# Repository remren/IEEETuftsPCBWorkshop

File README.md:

# IEEETuftsPCBWorkshop
An introductory PCB workshop for the Tufts IEEE club using KiCad 7.0. The basis for this workshop is making a keyboard PCB, following these guides: [Masterzen's Guide](https://www.masterzen.fr/2020/05/03/designing-a-keyboard-part-1/) and [ai03's Guide](https://wiki.ai03.com/books/pcb-design/page/pcb-guide-part-1---preparations)

By learning how to make this PCB, hopefully one will be able use knowledge for other personal or work projects!

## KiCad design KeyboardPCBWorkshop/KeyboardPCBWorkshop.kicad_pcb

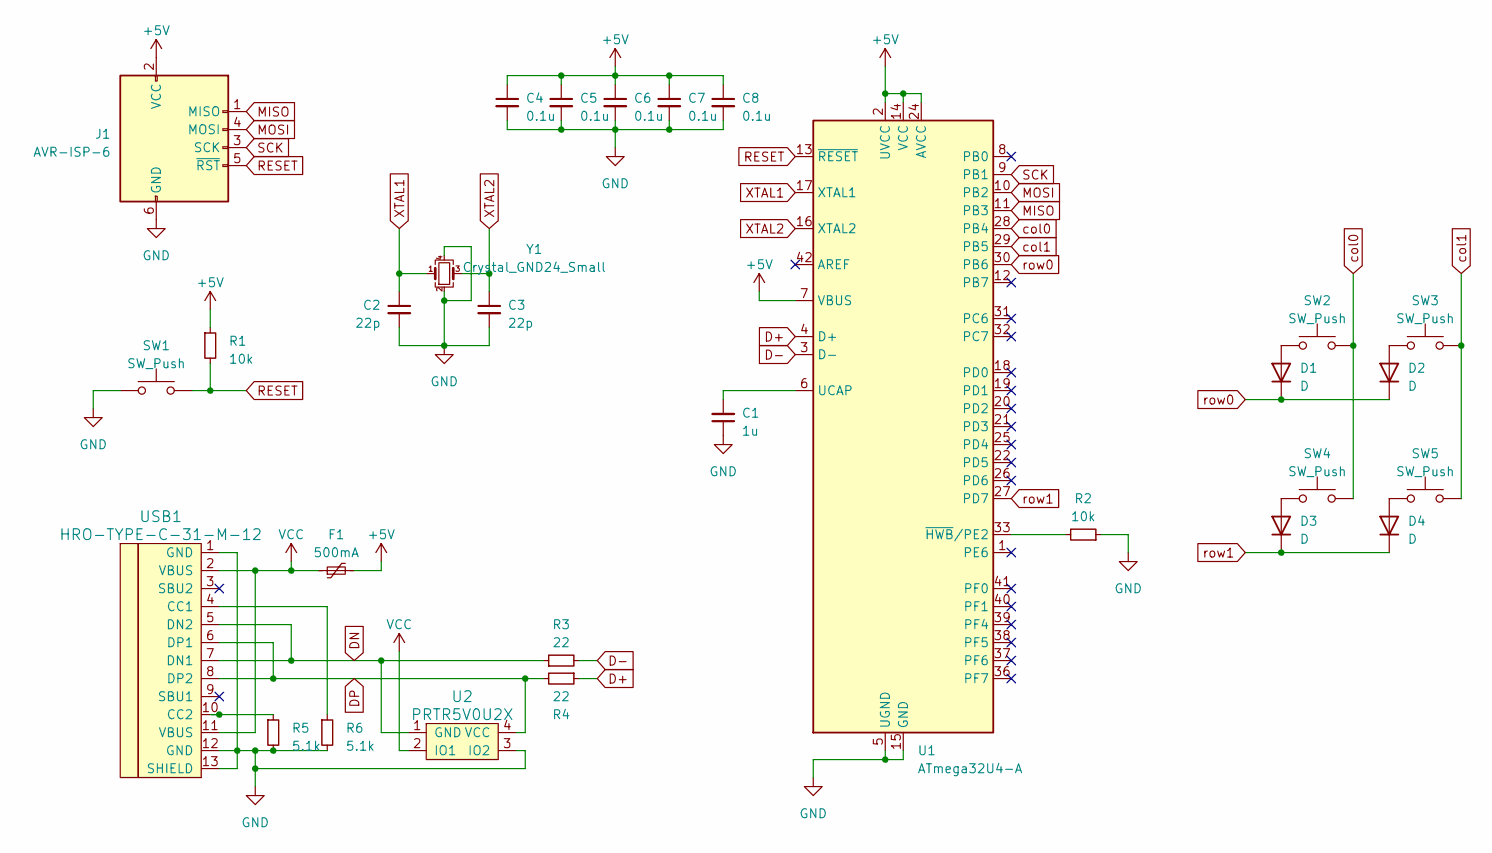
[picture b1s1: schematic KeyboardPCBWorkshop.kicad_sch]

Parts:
C1: 1u; C_0805_2012Metric_Pad1.18x1.45mm_HandSolder
C2, C3: 22p; C_0805_2012Metric_Pad1.18x1.45mm_HandSolder
C4, C5, C6, C7, C8: 0.1u; C_0805_2012Metric_Pad1.18x1.45mm_HandSolder
D1, D2, D3, D4: D; D_SOD-123
F1: 500mA; Fuse_1206_3216Metric_Pad1.42x1.75mm_HandSolder
J1: AVR-ISP-6; Reset_Pretty-Mask
R1, R2: 10k; R_0805_2012Metric_Pad1.20x1.40mm_HandSolder
R3, R4: 22; R_0805_2012Metric_Pad1.20x1.40mm_HandSolder
R5, R6: 5.1k; R_0805_2012Metric_Pad1.20x1.40mm_HandSolder
SW1: SW_Push; SW_SPST_SKQG_WithStem
SW2, SW3, SW4, SW5: SW_Push; MX-1U-NoLED
U1: ATmega32U4-A; TQFP-44_10x10mm_P0.8mm
U2: PRTR5V0U2X; SOT143B
USB1: HRO-TYPE-C-31-M-12; HRO-TYPE-C-31-M-12-HandSoldering
Y1: Crystal_GND24_Small; Crystal_SMD_3225-4Pin_3.2x2.5mm_HandSoldering

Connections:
+5V: C4.1, C5.1, C6.1, C7.1, C8.1, F1.2, J1.2 (VCC), R1.1, U1.2 (UVCC), U1.7 (VBUS), U1.14 (VCC), U1.24 (AVCC), U1.34 (VCC), U1.44 (AVCC)
D+: R4.1, U1.4 (D+)
D-: R3.2, U1.3 (D-)
DN: R3.1, U2.1 (GND), USB1.5 (DN2), USB1.7 (DN1)
DP: R4.2, U2.4 (VCC), USB1.6 (DP1), USB1.8 (DP2)
GND: C1.1, C2.2, C3.2, C4.2, C5.2, C6.2, C7.2, C8.2, J1.6 (GND), R2.1, R5.2, R6.2, SW1.1, U1.5 (UGND), U1.15 (GND), U1.23 (GND), U1.35 (GND), U1.43 (GND), U2.3 (IO2), USB1.1 (GND), USB1.12 (GND), USB1.13 (SHIELD), Y1.2, Y1.4
MISO: J1.1 (MISO), U1.11 (PB3)
MOSI: J1.4 (MOSI), U1.10 (PB2)
unnamed: D1.2 (A), SW2.2
unnamed: D2.2 (A), SW3.2
unnamed: D3.2 (A), SW4.2
unnamed: D4.2 (A), SW5.2
unnamed: C1.2, U1.6 (UCAP)
unnamed: R2.2, U1.33 (~HWB/PE2)
unnamed: R6.1, USB1.4 (CC1)
unnamed: R5.1, USB1.10 (CC2)
RESET: J1.5 (~RST), R1.2, SW1.2, U1.13 (~RESET)
SCK: J1.3 (SCK), U1.9 (PB1)
VCC: F1.1, U2.2 (IO1), USB1.2 (VBUS), USB1.11 (VBUS)
XTAL1: C2.1, U1.17 (XTAL1), Y1.1
XTAL2: C3.1, U1.16 (XTAL2), Y1.3
col0: SW2.1, SW4.1, U1.28 (PB4)
col1: SW3.1, SW5.1, U1.29 (PB5)
row0: D1.1 (K), D2.1 (K), U1.30 (PB6)
row1: D3.1 (K), D4.1 (K), U1.27 (PD7)

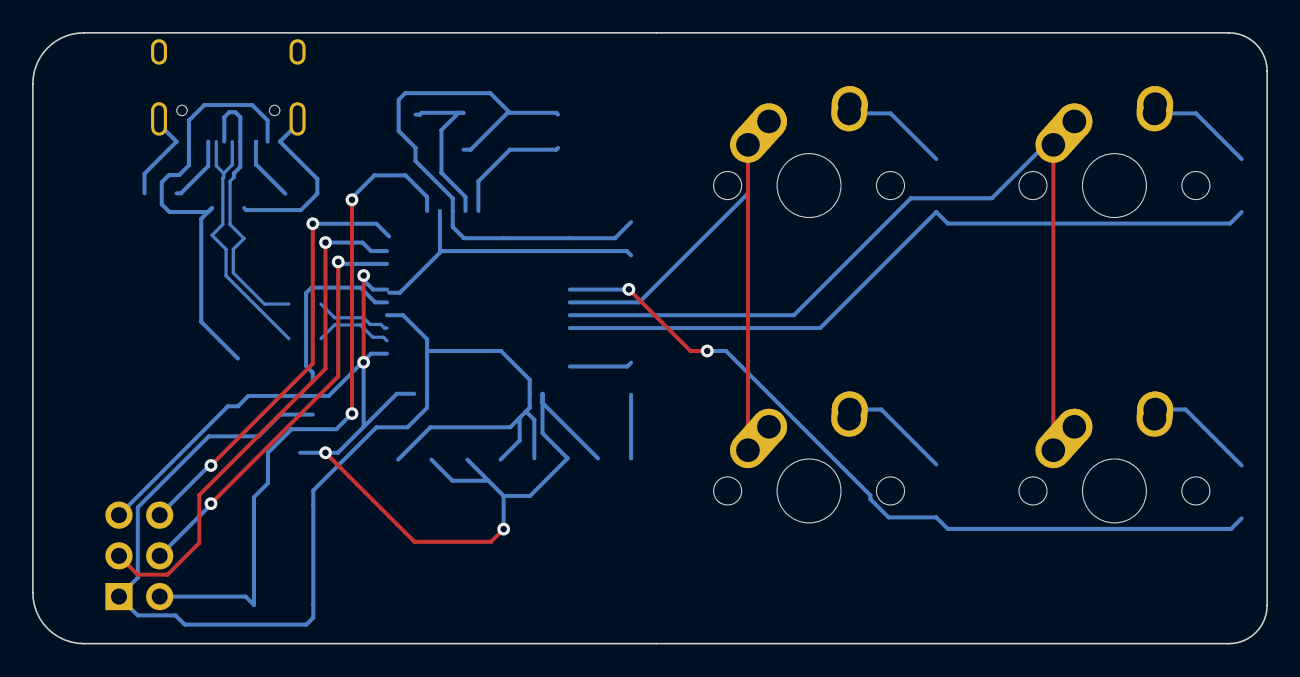
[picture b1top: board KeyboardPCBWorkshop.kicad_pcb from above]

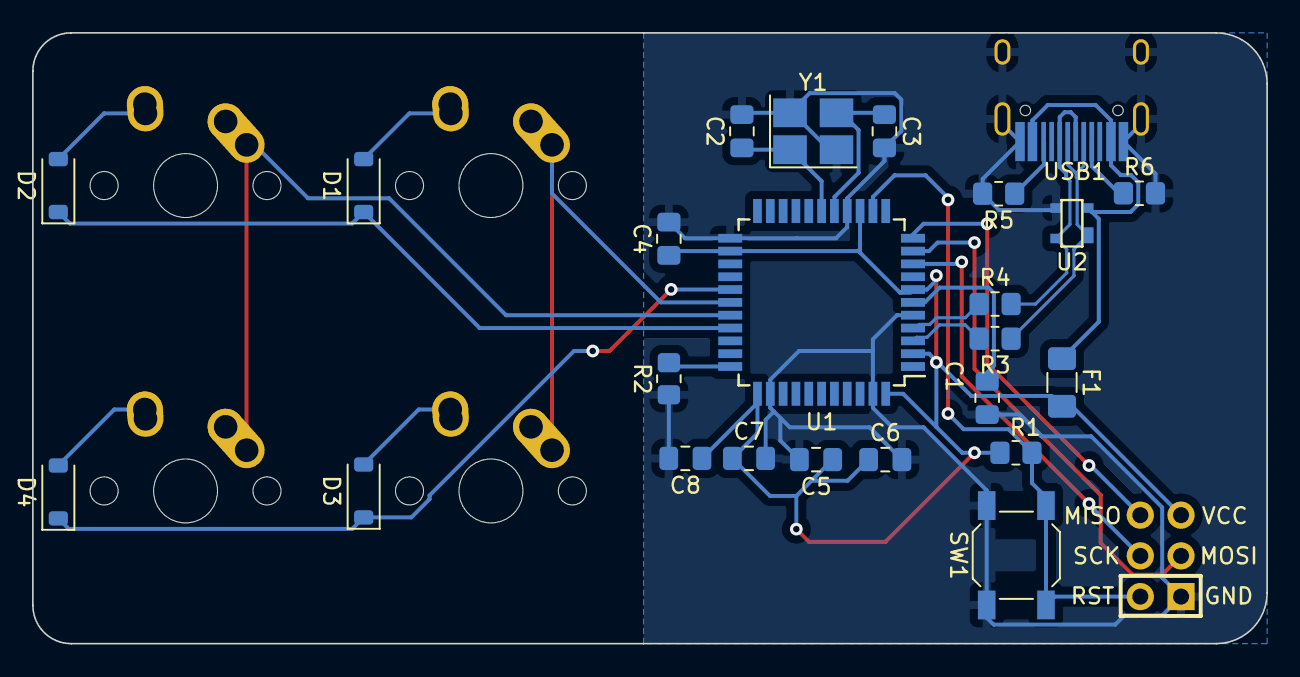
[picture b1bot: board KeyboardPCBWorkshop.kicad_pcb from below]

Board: 2 copper layers, 77.0 x 38.1 mm, 29 parts (25 on the bottom side), 25 nets.

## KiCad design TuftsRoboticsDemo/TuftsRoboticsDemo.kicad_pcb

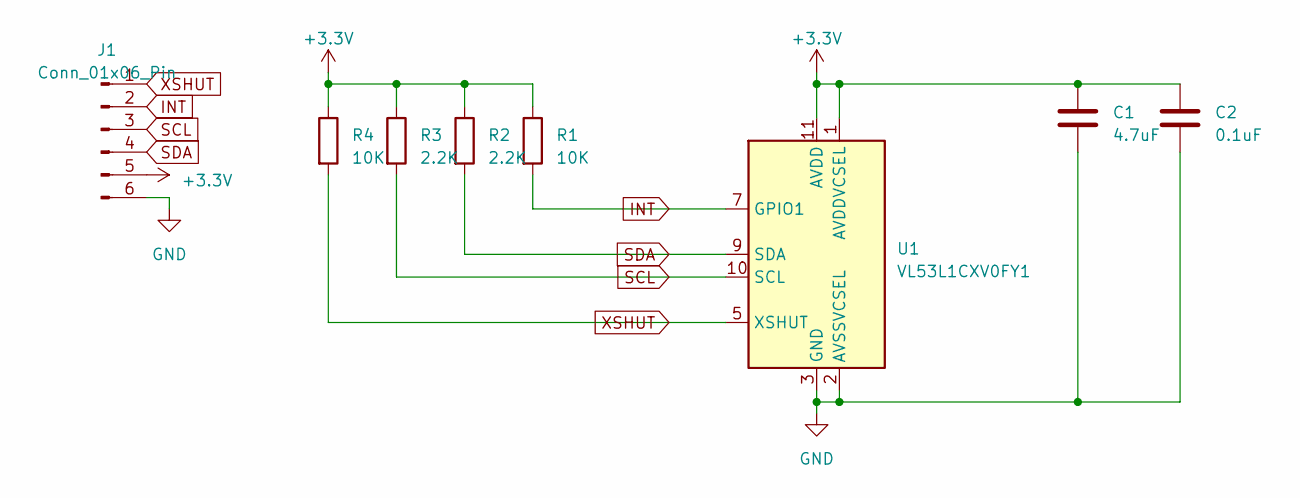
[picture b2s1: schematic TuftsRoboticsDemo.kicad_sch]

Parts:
C1: 4.7uF; C_0603_1608Metric
C2: 0.1uF; C_0603_1608Metric
J1: Conn_01x06_Pin; PinHeader_1x06_P2.54mm_Vertical
R1, R4: 10K; R_0603_1608Metric
R2, R3: 2.2K; R_0603_1608Metric
U1: VL53L1CXV0FY1; ST_VL53L1x

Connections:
+3.3V: C1.1, C2.1, J1.5, R1.1, R2.1, R3.1, R4.1, U1.1 (AVDDVCSEL), U1.11 (AVDD)
GND: C1.2, C2.2, J1.6, U1.2 (AVSSVCSEL), U1.3 (GND), U1.4 (GND), U1.6 (GND), U1.12 (GND)
INT: J1.2, R1.2, U1.7 (GPIO1)
SCL: J1.3, R3.2, U1.10 (SCL)
SDA: J1.4, R2.2, U1.9 (SDA)
XSHUT: J1.1, R4.2, U1.5 (XSHUT)

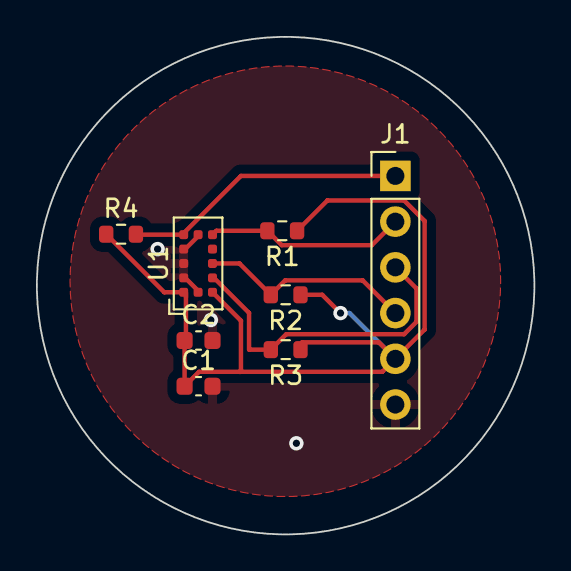
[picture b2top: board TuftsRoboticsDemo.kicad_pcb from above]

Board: 2 copper layers, 27.6 x 27.6 mm, 8 parts (0 on the bottom side), 6 nets.

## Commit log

2023-04-15 first github commit
2023-04-16 Initial Files
2023-04-16 Tufts Robotics Reference
2023-04-16 ai03 MX/Alps switch footprint library
2023-04-16 ai03 usb c connectors and random parts
2023-04-17 Add git and github tutorial PDF
2023-04-17 Reorganize and PDF Guides
2023-04-17 odd submodule behavior
2023-04-17 readded submodules
2023-04-17 update breakout PCB
2023-04-17 PCB update
2023-04-18 remove extraneous tufts robotics demo
2023-04-18 added XTAL, coupling cap, ISP header
2023-04-18 Added reset circuit and USB port
2023-04-18 keyboard matrix
2023-04-19 completed switch matrices
2023-04-19 footprint libraries connected
2023-04-19 assigned footprints
2023-04-19 keyboard placement
2023-04-19 Additional PCB changes
2023-04-20 routing complete
2023-04-20 FINISHED w/ERRORS?
2023-04-20 rough draft of PCB guide
2023-04-20 Final Commit Before Workshop
2023-04-21 edit to guide pdf
